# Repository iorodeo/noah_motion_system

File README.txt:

NOAH Motion System

Design files, software and firmware for the NOAH water tunnel motion control system.

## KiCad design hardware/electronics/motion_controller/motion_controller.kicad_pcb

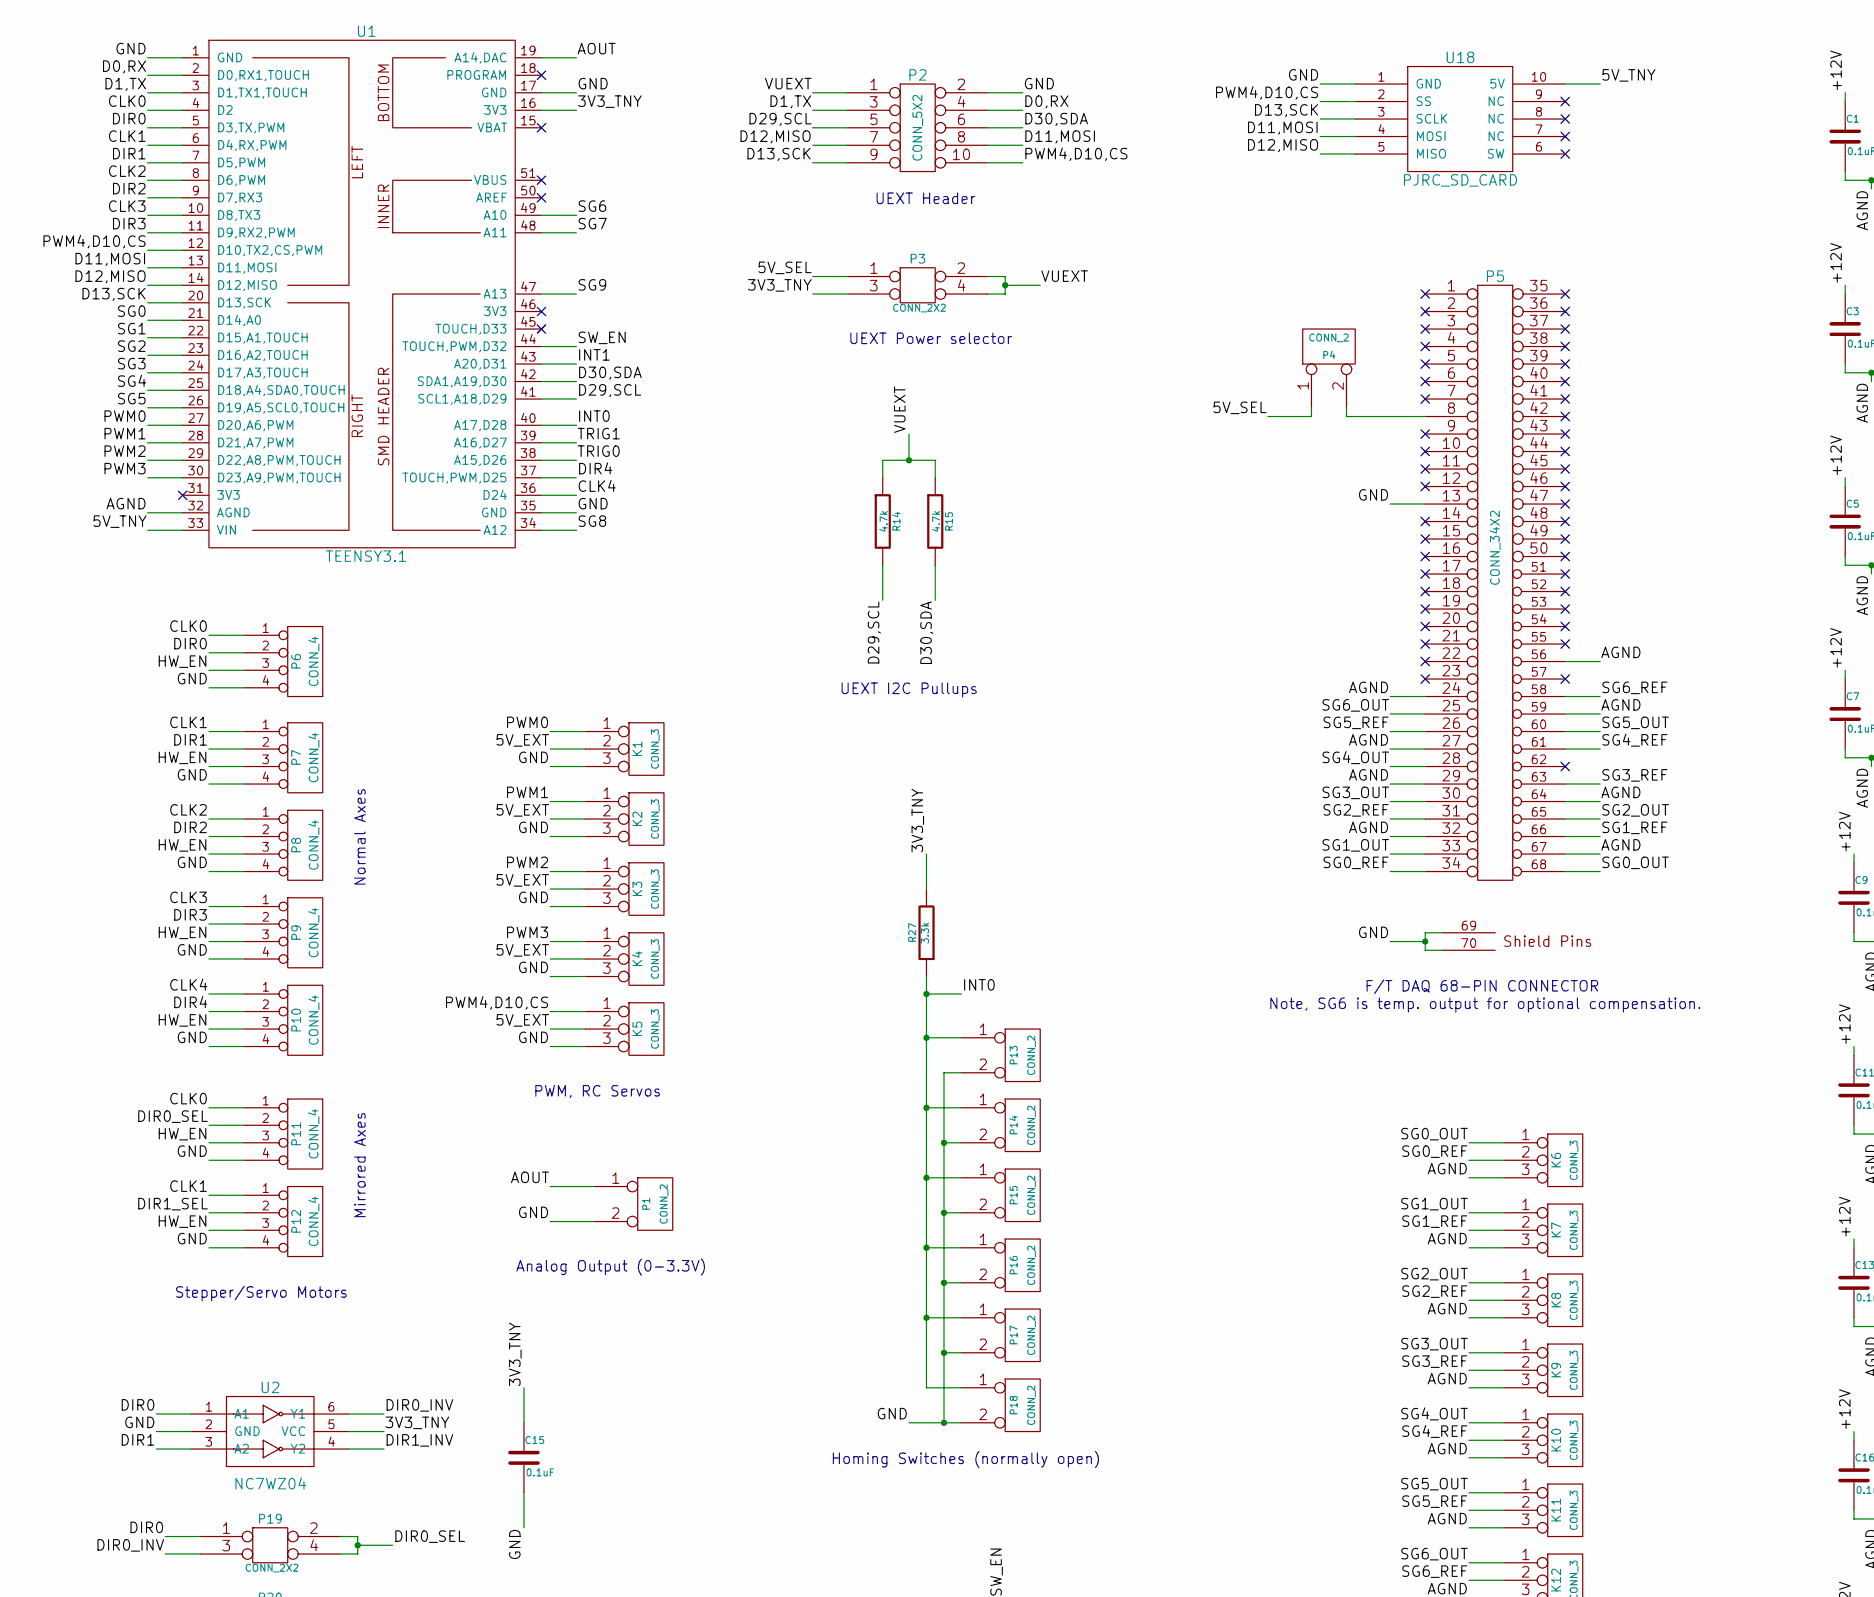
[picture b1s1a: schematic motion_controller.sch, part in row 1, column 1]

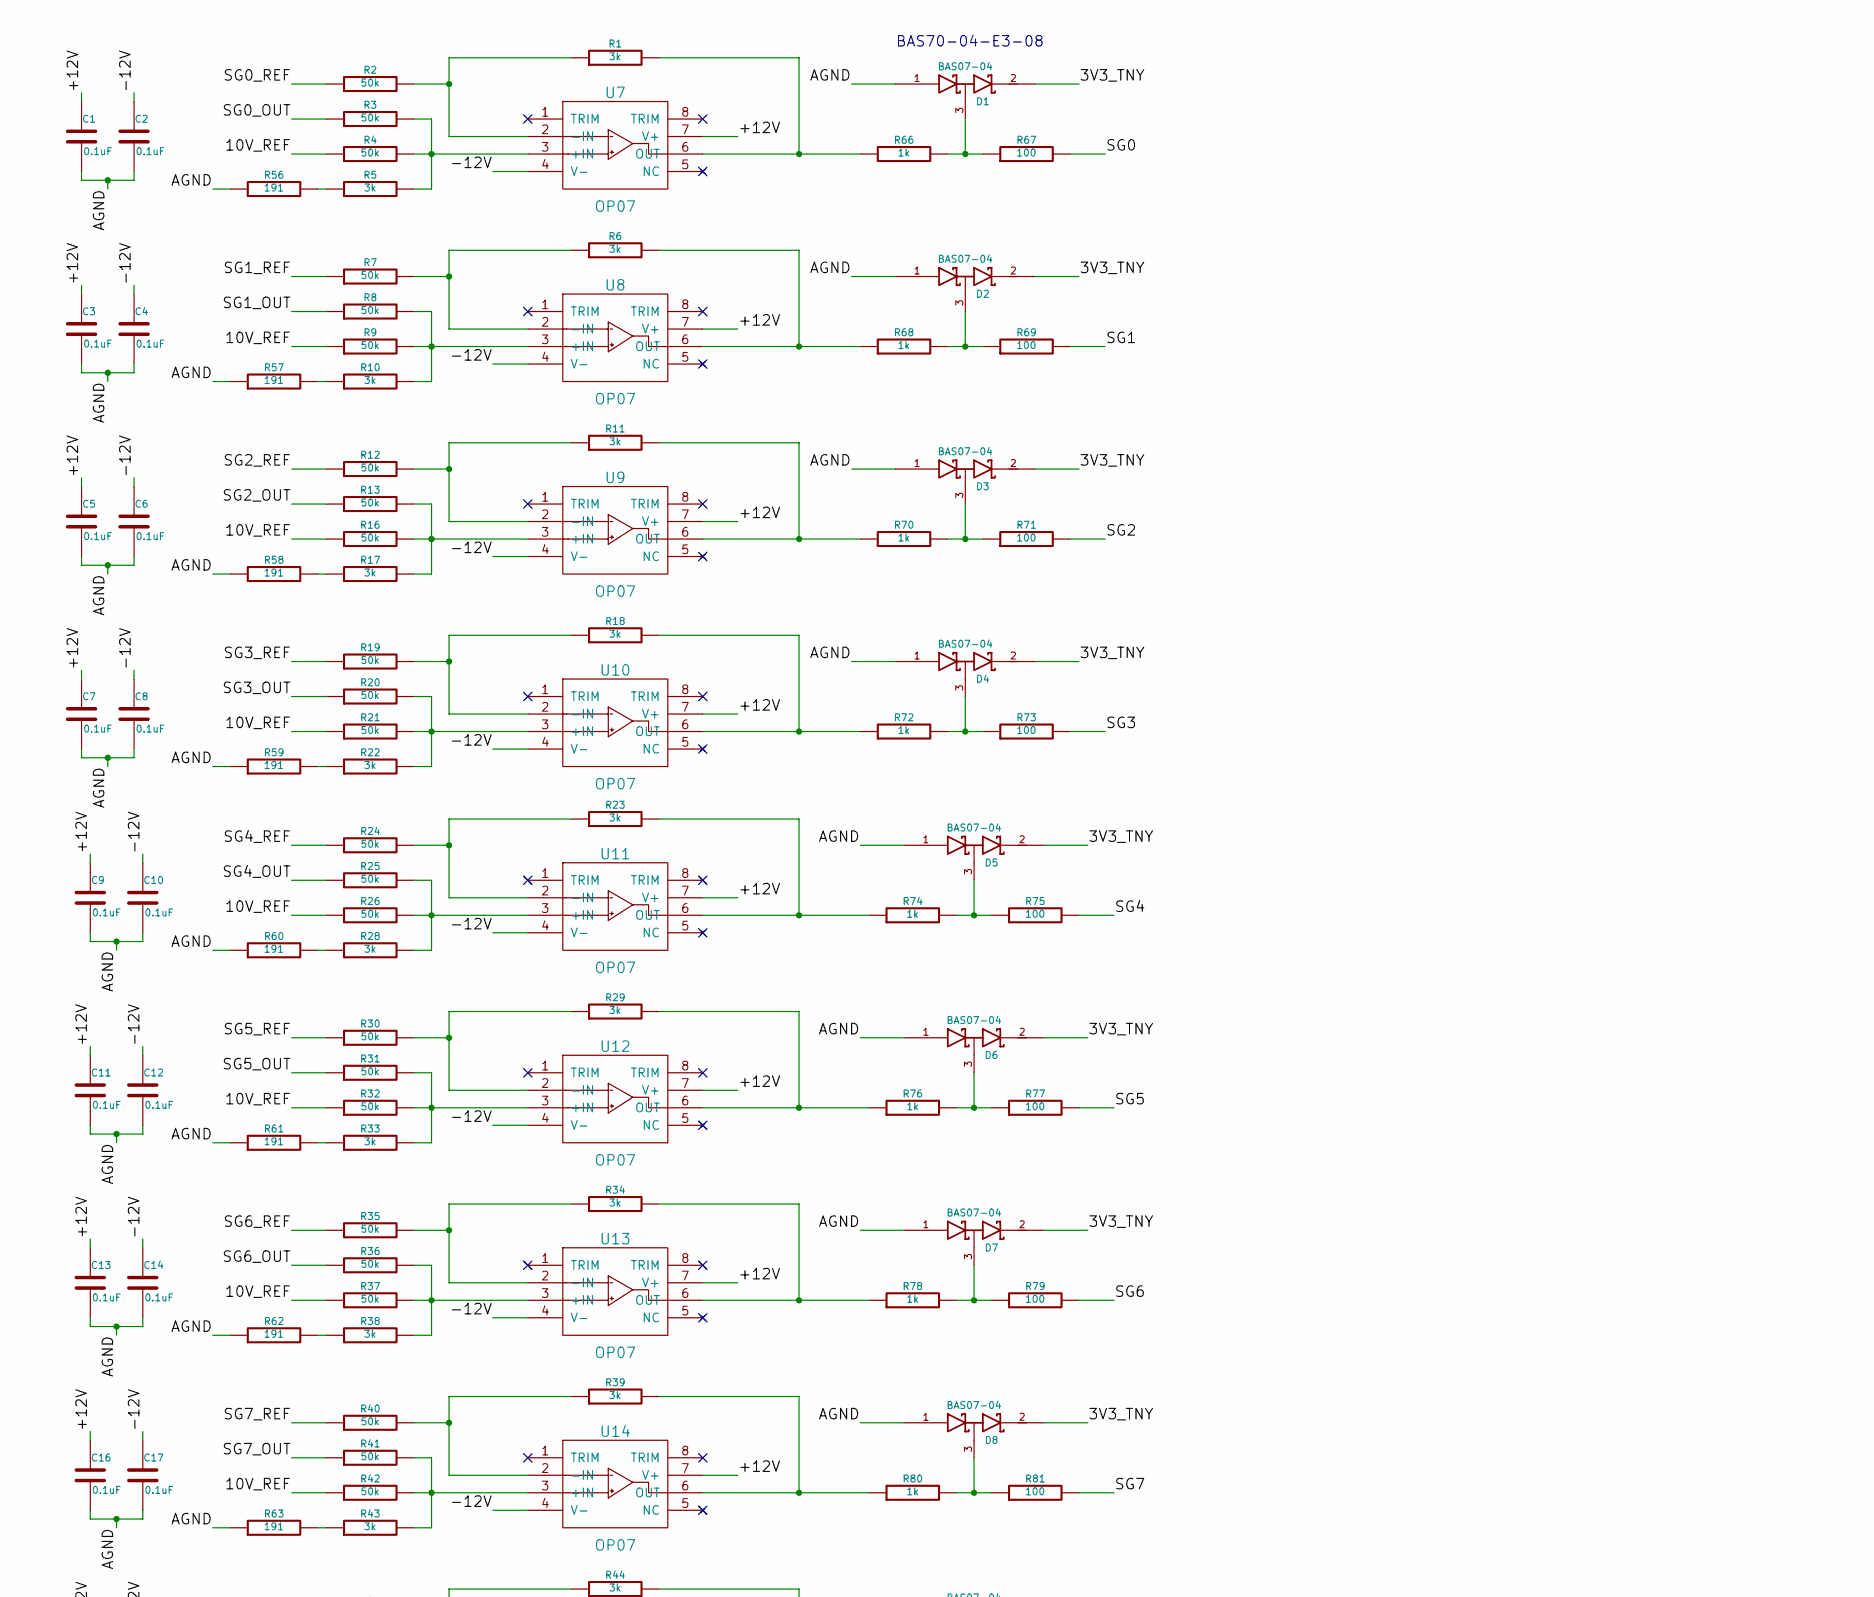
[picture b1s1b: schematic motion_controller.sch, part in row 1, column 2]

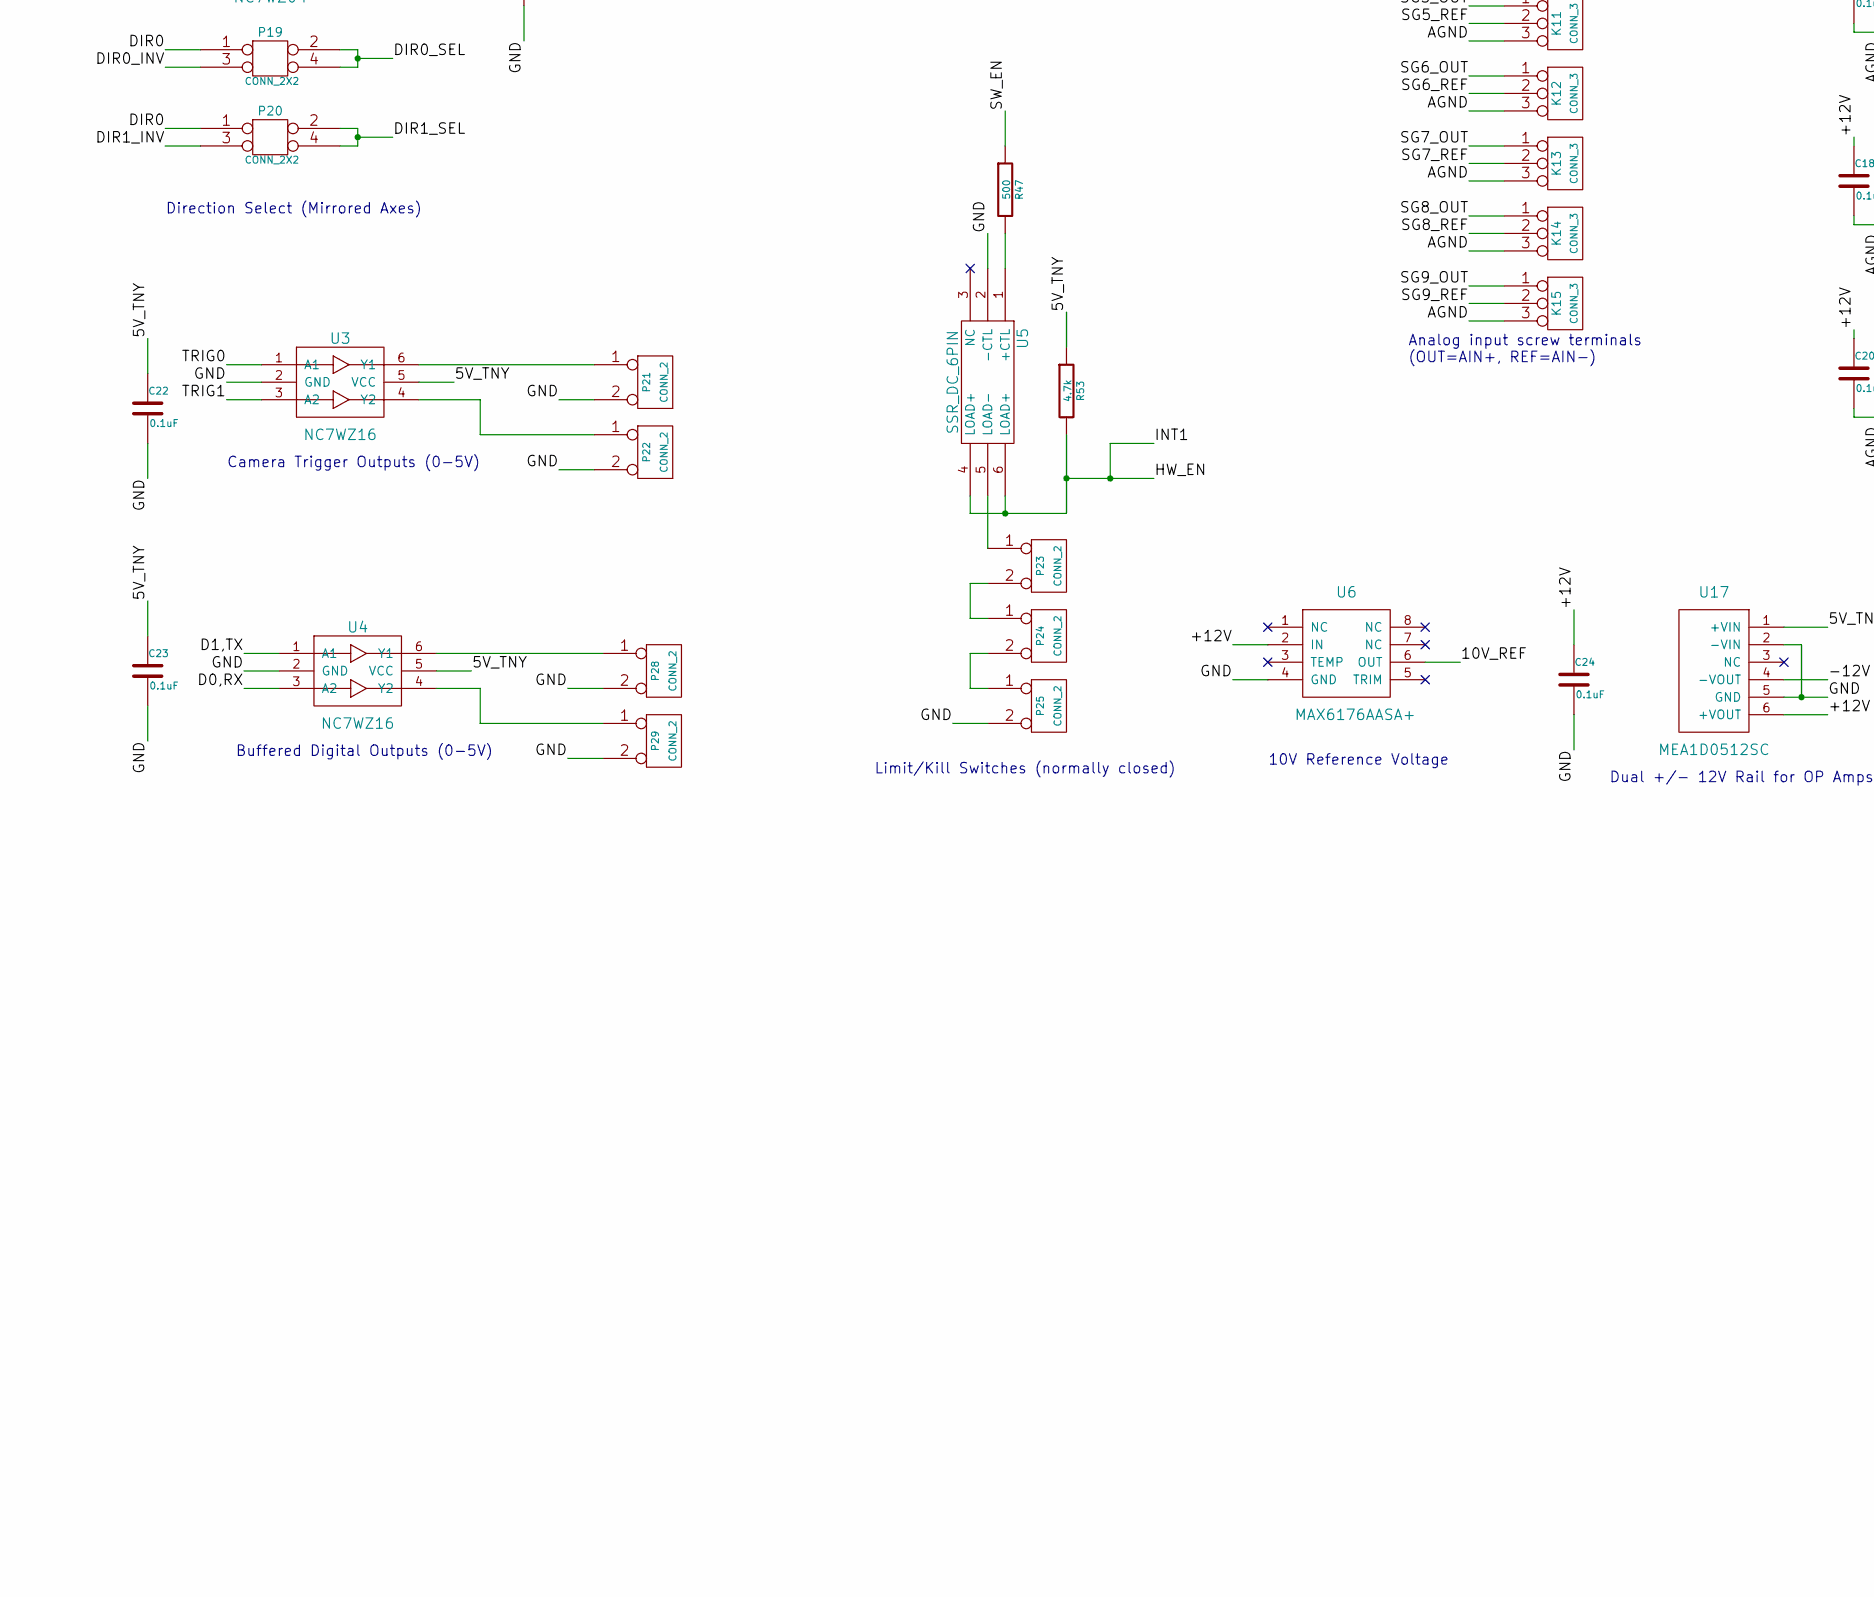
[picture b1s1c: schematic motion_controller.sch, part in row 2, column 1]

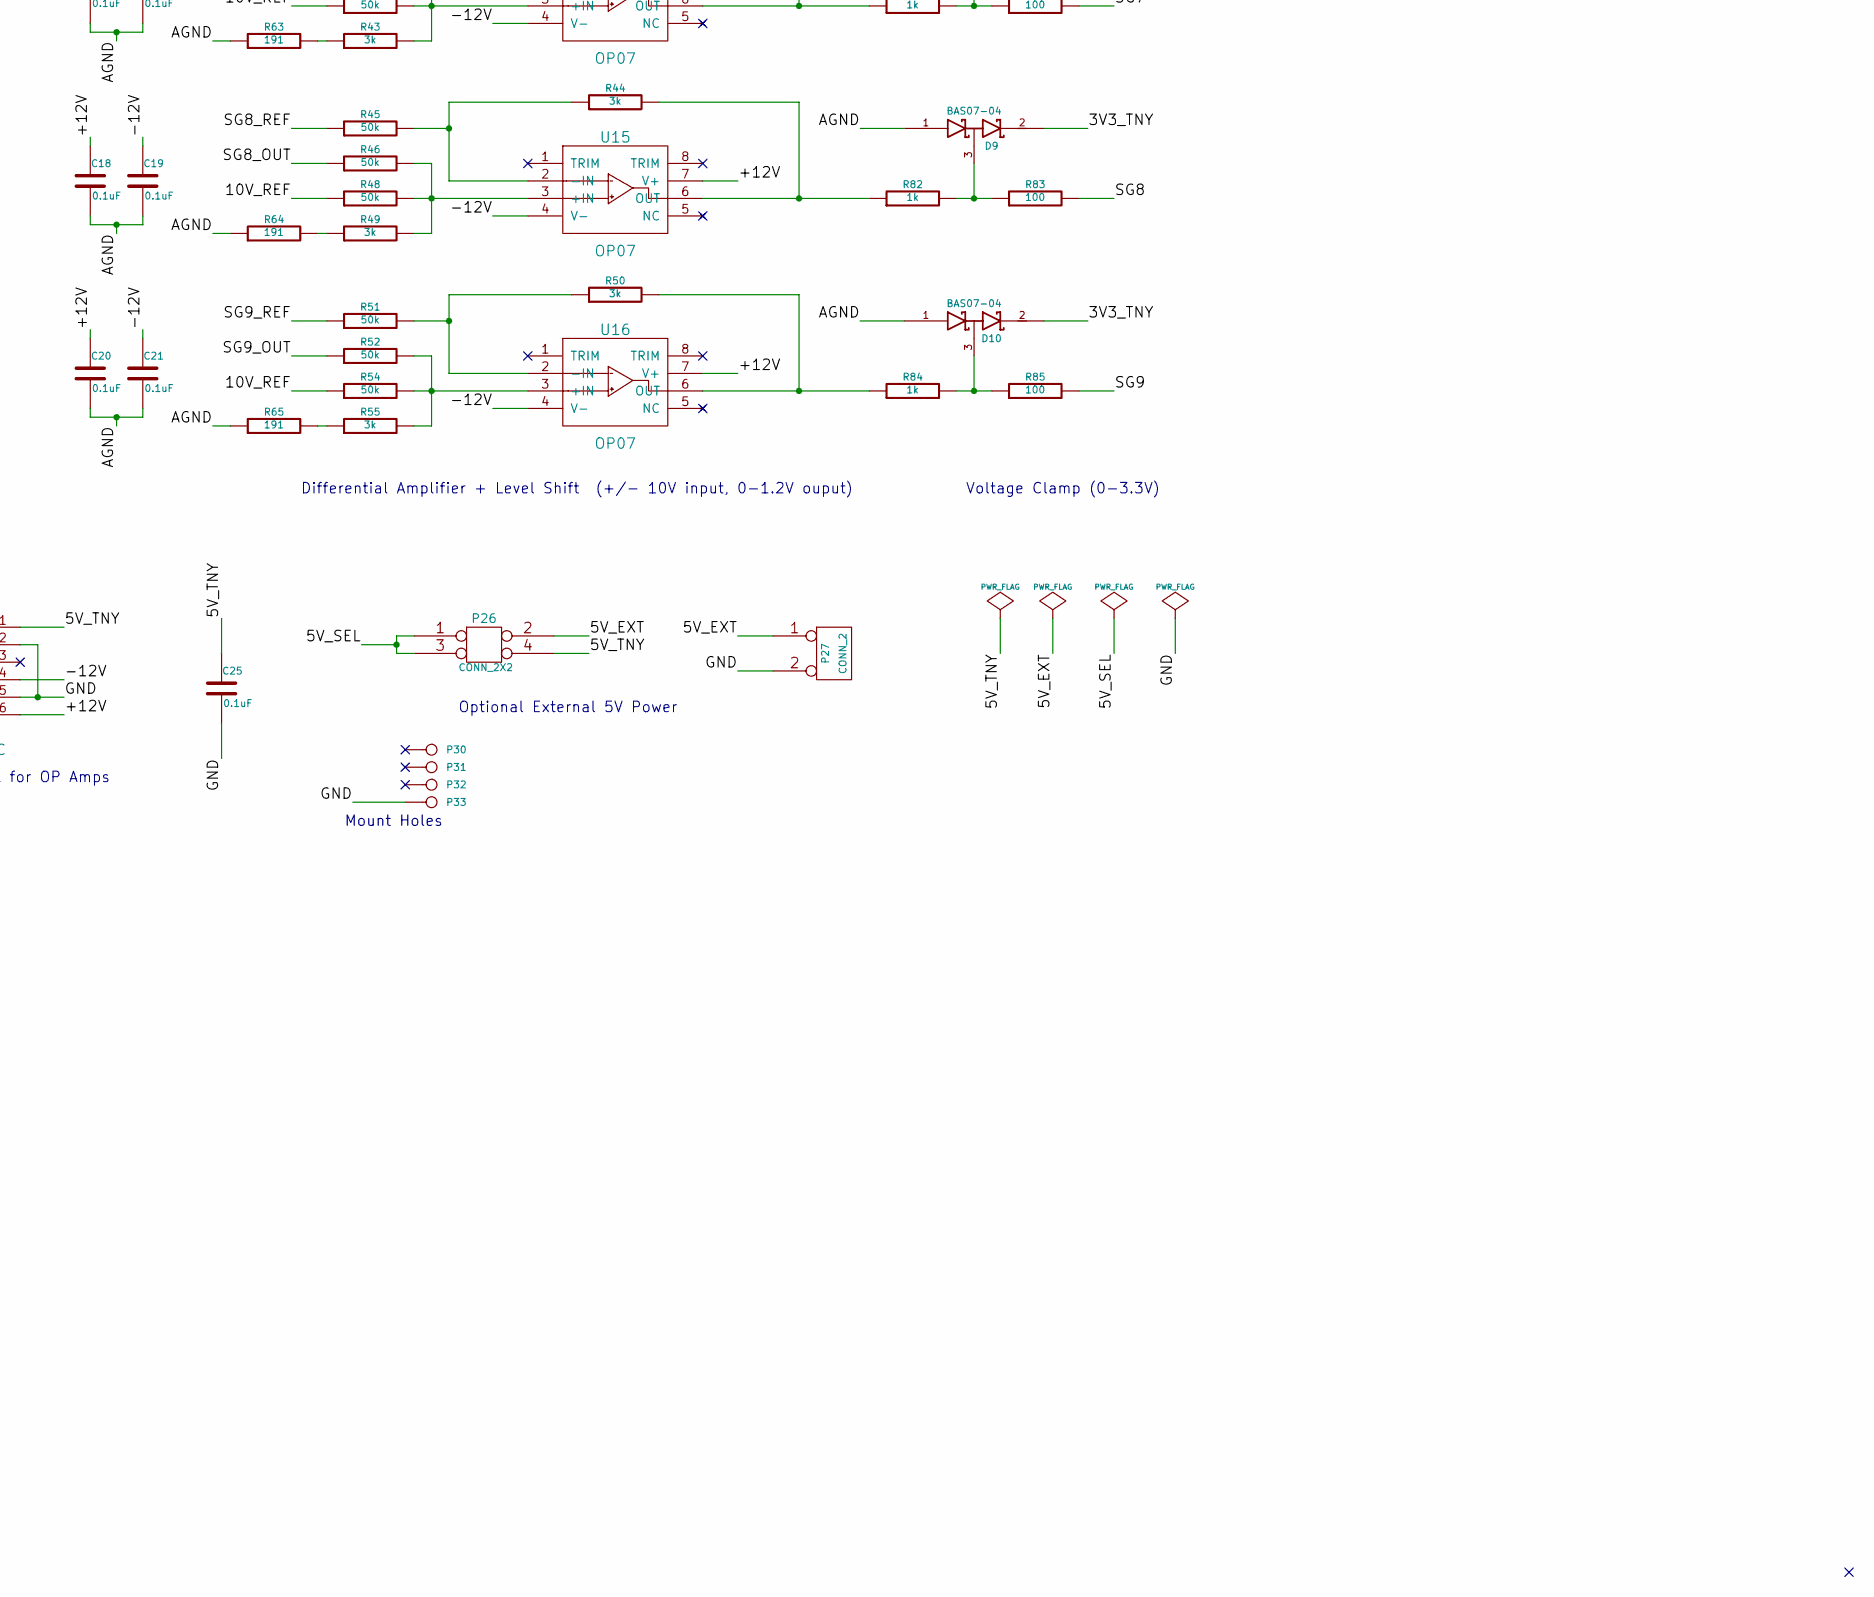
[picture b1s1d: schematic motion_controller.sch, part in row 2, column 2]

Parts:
C1, C2, C3, C4, C5, C6, C7, C8, C9, C10, C11, C12, C13, C14, C15, C16, C17, C18, C19, C20, C21, C22, C23, C24, C25: 0.1uF
D1, D2, D3, D4, D5, D6, D7, D8, D9, D10: BAS07-04
K1, K2, K3, K4, K5, K6, K7, K8, K9, K10, K11, K12, K13, K14, K15: CONN_3
P1, P4, P13, P14, P15, P16, P17, P18, P21, P22, P23, P24, P25, P27, P28, P29: CONN_2
P2: CONN_5X2
P3, P19, P20, P26: CONN_2X2
P5: CONN_34X2
P6, P7, P8, P9, P10, P11, P12: CONN_4
P30, P31, P32, P33: CONN_1
R1, R5, R6, R10, R11, R17, R18, R22, R23, R28, R29, R33, R34, R38, R39, R43, R44, R49, R50, R55: 3k
R2, R3, R4, R7, R8, R9, R12, R13, R16, R19, R20, R21, R24, R25, R26, R30, R31, R32, R35, R36, R37, R40, R41, R42, R45, R46, R48, R51, R52, R54: 50k
R14, R15, R53: 4.7k
R27: 3.3k
R47: 500
R56, R57, R58, R59, R60, R61, R62, R63, R64, R65: 191
R66, R68, R70, R72, R74, R76, R78, R80, R82, R84: 1k
R67, R69, R71, R73, R75, R77, R79, R81, R83, R85: 100
U1: TEENSY3.1
U2: NC7WZ04
U3, U4: NC7WZ16
U5: SSR_DC_6PIN
U6: MAX6176AASA+
U7, U8, U9, U10, U11, U12, U13, U14, U15, U16: OP07
U17: MEA1D0512SC
U18: PJRC_SD_CARD

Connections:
/3V3_TNY: C15.1, D1.2 (cathode), D2.2 (cathode), D3.2 (cathode), D4.2 (cathode), D5.2 (cathode), D6.2 (cathode), D7.2 (cathode), D8.2 (cathode), D9.2 (cathode), D10.2 (cathode), P3.3, R27.2, U1.16 (3V3), U2.5 (VCC)
/5V_EXT: K1.2 (PM), K2.2 (PM), K3.2 (PM), K4.2 (PM), K5.2 (PM), P26.2, P27.1
/5V_SEL: P3.1, P4.1, P26.1, P26.3
/5V_TNY: C22.1, C23.1, C25.1, P26.4, R53.1, U1.33 (VIN), U3.5 (VCC), U4.5 (VCC), U17.1 (+VIN), U18.10 (5V)
/10V_REF: R4.1, R9.1, R16.1, R21.1, R26.1, R32.1, R37.1, R42.1, R48.1, R54.1, U6.6 (OUT)
/+12V: C1.1, C3.1, C5.1, C7.1, C9.1, C11.1, C13.1, C16.1, C18.1, C20.1, C24.1, U6.2 (IN), U7.7 (V+), U8.7 (V+), U9.7 (V+), U10.7 (V+), U11.7 (V+), U12.7 (V+), U13.7 (V+), U14.7 (V+), U15.7 (V+), U16.7 (V+), U17.6 (+VOUT)
/-12V: C2.1, C4.1, C6.1, C8.1, C10.1, C12.1, C14.1, C17.1, C19.1, C21.1, U7.4 (V-), U8.4 (V-), U9.4 (V-), U10.4 (V-), U11.4 (V-), U12.4 (V-), U13.4 (V-), U14.4 (V-), U15.4 (V-), U16.4 (V-), U17.4 (-VOUT)
/AGND: C1.2, C2.2, C3.2, C4.2, C5.2, C6.2, C7.2, C8.2, C9.2, C10.2, C11.2, C12.2, C13.2, C14.2, C16.2, C17.2, C18.2, C19.2, C20.2, C21.2, D1.1 (Anode), D2.1 (Anode), D3.1 (Anode), D4.1 (Anode), D5.1 (Anode), D6.1 (Anode), D7.1 (Anode), D8.1 (Anode), D9.1 (Anode), D10.1 (Anode), K6.3, K7.3, K8.3, K9.3, K10.3, K11.3, K12.3, K13.3, K14.3, K15.3, P5.24, P5.27, P5.29, P5.32, P5.56, P5.59, P5.64, P5.67, R56.1, R57.1, R58.1, R59.1, R60.1, R61.1, R62.1, R63.1, R64.1, R65.1, U1.32 (AGND)
/AOUT: P1.1, U1.19 (A14,DAC)
/CLK0: P6.1, P11.1, U1.4 (D2)
/CLK1: P7.1, P12.1, U1.6 (D4,RX,PWM)
/CLK2: P8.1, U1.8 (D6,PWM)
/CLK3: P9.1, U1.10 (D8,TX3)
/CLK4: P10.1, U1.36 (D24)
/D0,RX: P2.4, U1.2 (D0,RX1,TOUCH), U4.3 (A2)
/D1,TX: P2.3, U1.3 (D1,TX1,TOUCH), U4.1 (A1)
/D11,MOSI: P2.8, U1.13 (D11,MOSI), U18.4 (MOSI)
/D12,MISO: P2.7, U1.14 (D12,MISO), U18.5 (MISO)
/D13,SCK: P2.9, U1.20 (D13,SCK), U18.3 (SCLK)
/D29,SCL: P2.5, R14.2, U1.41 (SCL1,A18,D29)
/D30,SDA: P2.6, R15.2, U1.42 (SDA1,A19,D30)
/DIR0: P6.2, P19.1, P20.1, U1.5 (D3,TX,PWM), U2.1 (A1)
/DIR0_INV: P19.3, U2.6 (Y1)
/DIR0_SEL: P11.2, P19.2, P19.4
/DIR1: P7.2, U1.7 (D5,PWM), U2.3 (A2)
/DIR1_INV: P20.3, U2.4 (Y2)
/DIR1_SEL: P12.2, P20.2, P20.4
/DIR2: P8.2, U1.9 (D7,RX3)
/DIR3: P9.2, U1.11 (D9,RX2,PWM)
/DIR4: P10.2, U1.37 (TOUCH,PWM,D25)
/GND: C15.2, C22.2, C23.2, C24.2, C25.2, K1.3, K2.3, K3.3, K4.3, K5.3, P1.2 (PM), P2.2, P5.13, P5.69, P5.70, P6.4, P7.4, P8.4, P9.4, P10.4, P11.4, P12.4, P13.2 (PM), P14.2 (PM), P15.2 (PM), P16.2 (PM), P17.2 (PM), P18.2 (PM), P21.2 (PM), P22.2 (PM), P25.2 (PM), P27.2 (PM), P28.2 (PM), P29.2 (PM), P33.1, U1.1 (GND), U1.17 (GND), U1.35 (GND), U2.2 (GND), U3.2 (GND), U4.2 (GND), U5.2 (-CTL), U6.4 (GND), U17.2 (-VIN), U17.5 (GND), U18.1 (GND)
/HW_EN: P6.3, P7.3, P8.3, P9.3, P10.3, P11.3, P12.3, R53.2, U1.43 (A20,D31), U5.4 (LOAD+), U5.6 (LOAD+)
/INT0: P13.1, P14.1, P15.1, P16.1, P17.1, P18.1, R27.1, U1.40 (A17,D28)
/PWM0: K1.1, U1.27 (D20,A6,PWM)
/PWM1: K2.1, U1.28 (D21,A7,PWM)
/PWM2: K3.1, U1.29 (D22,A8,PWM,TOUCH)
/PWM3: K4.1, U1.30 (D23,A9,PWM,TOUCH)
/PWM4,D10,CS: K5.1, P2.10, U1.12 (D10,TX2,CS,PWM), U18.2 (SS)
/SG0: R67.2, U1.21 (D14,A0)
/SG0_OUT: K6.1, P5.68, R3.1
/SG0_REF: K6.2 (PM), P5.34, R2.1
/SG1: R69.2, U1.22 (D15,A1,TOUCH)
/SG1_OUT: K7.1, P5.33, R8.1
/SG1_REF: K7.2 (PM), P5.66, R7.1
/SG2: R71.2, U1.23 (D16,A2,TOUCH)
/SG2_OUT: K8.1, P5.65, R13.1
/SG2_REF: K8.2 (PM), P5.31, R12.1
/SG3: R73.2, U1.24 (D17,A3,TOUCH)
/SG3_OUT: K9.1, P5.30, R20.1
/SG3_REF: K9.2 (PM), P5.63, R19.1
/SG4: R75.2, U1.25 (D18,A4,SDA0,TOUCH)
/SG4_OUT: K10.1, P5.28, R25.1
/SG4_REF: K10.2 (PM), P5.61, R24.1
/SG5: R77.2, U1.26 (D19,A5,SCL0,TOUCH)
/SG5_OUT: K11.1, P5.60, R31.1
/SG5_REF: K11.2 (PM), P5.26, R30.1
/SG6: R79.2, U1.49 (A10)
/SG6_OUT: K12.1, P5.25, R36.1
/SG6_REF: K12.2 (PM), P5.58, R35.1
/SG7: R81.2, U1.48 (A11)
/SG7_OUT: K13.1, R41.1
/SG7_REF: K13.2 (PM), R40.1
/SG8: R83.2, U1.34 (A12)
/SG8_OUT: K14.1, R46.1
/SG8_REF: K14.2 (PM), R45.1
/SG9: R85.2, U1.47 (A13)
/SG9_OUT: K15.1, R52.1
/SG9_REF: K15.2 (PM), R51.1
/SW_EN: R47.1, U1.44 (TOUCH,PWM,D32)
/TRIG0: U1.38 (A15,D26), U3.1 (A1)
/TRIG1: U1.39 (A16,D27), U3.3 (A2)
/VUEXT: P2.1, P3.2, P3.4, R14.1, R15.1
unnamed: P21.1, U3.6 (Y1)
unnamed: R47.2, U5.1 (+CTL)
unnamed: P23.1, U5.5 (LOAD-)
unnamed: P29.1, U4.4 (Y2)
unnamed: P28.1, U4.6 (Y1)
unnamed: P22.1, U3.4 (Y2)
unnamed: P23.2 (PM), P24.1
unnamed: P24.2 (PM), P25.1
unnamed: R20.2, R21.2, R22.2, U10.3 (+IN)
unnamed: R18.2, R72.1, U10.6 (OUT)
unnamed: R18.1, R19.2, U10.2 (-IN)
unnamed: R13.2, R16.2, R17.2, U9.3 (+IN)
unnamed: R11.2, R70.1, U9.6 (OUT)
unnamed: R29.2, R76.1, U12.6 (OUT)
unnamed: R25.2, R26.2, R28.2, U11.3 (+IN)
unnamed: R23.2, R74.1, U11.6 (OUT)
unnamed: R23.1, R24.2, U11.2 (-IN)
unnamed: R1.2, R66.1, U7.6 (OUT)
unnamed: R1.1, R2.2, U7.2 (-IN)
unnamed: R11.1, R12.2, U9.2 (-IN)
unnamed: R8.2, R9.2, R10.2, U8.3 (+IN)
unnamed: R6.2, R68.1, U8.6 (OUT)
unnamed: R6.1, R7.2, U8.2 (-IN)
unnamed: R3.2, R4.2, R5.2, U7.3 (+IN)
unnamed: R33.1, R61.2
unnamed: R49.1, R64.2
unnamed: R43.1, R63.2
unnamed: R38.1, R62.2
unnamed: R28.1, R60.2
unnamed: R22.1, R59.2
unnamed: R17.1, R58.2
unnamed: R10.1, R57.2
unnamed: P4.2 (PM), P5.8
unnamed: D1.3 (AK), R66.2, R67.1
unnamed: R55.1, R65.2
unnamed: R50.1, R51.2, U16.2 (-IN)
unnamed: R5.1, R56.2
unnamed: D4.3 (AK), R72.2, R73.1
unnamed: D3.3 (AK), R70.2, R71.1
unnamed: D6.3 (AK), R76.2, R77.1
unnamed: D5.3 (AK), R74.2, R75.1
unnamed: D2.3 (AK), R68.2, R69.1
unnamed: R34.2, R78.1, U13.6 (OUT)
unnamed: D10.3 (AK), R84.2, R85.1
unnamed: D8.3 (AK), R80.2, R81.1
unnamed: R39.2, R80.1, U14.6 (OUT)
unnamed: D7.3 (AK), R78.2, R79.1
unnamed: D9.3 (AK), R82.2, R83.1
unnamed: R50.2, R84.1, U16.6 (OUT)
unnamed: R44.2, R82.1, U15.6 (OUT)
unnamed: R46.2, R48.2, R49.2, U15.3 (+IN)
unnamed: R36.2, R37.2, R38.2, U13.3 (+IN)
unnamed: R34.1, R35.2, U13.2 (-IN)
unnamed: R31.2, R32.2, R33.2, U12.3 (+IN)
unnamed: R29.1, R30.2, U12.2 (-IN)
unnamed: R41.2, R42.2, R43.2, U14.3 (+IN)
unnamed: R44.1, R45.2, U15.2 (-IN)
unnamed: R39.1, R40.2, U14.2 (-IN)
unnamed: R52.2, R54.2, R55.2, U16.3 (+IN)

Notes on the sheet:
F/T DAQ 68-PIN CONNECTOR
Note, SG6 is temp. output for optional compensation.
Analog input screw terminals (OUT=AIN+, REF=AIN-)
UEXT Header
UEXT Power selector
Homing Switches (normally open)
Limit/Kill Switches (normally closed)
Optional External 5V Power
PWM, RC Servos
Camera Trigger Outputs (0-5V)
UEXT I2C Pullups
Buffered Digital Outputs (0-5V)
Stepper/Servo Motors
Differential Amplifier + Level Shift (+/- 10V input, 0-1.2V ouput)
Normal Axes
Mirrored Axes
Dual +/- 12V Rail for OP Amps
10V Reference Voltage
Voltage Clamp (0-3.3V)
Analog Output (0-3.3V)
Direction Select (Mirrored Axes)
BAS70-04-E3-08
Mount Holes

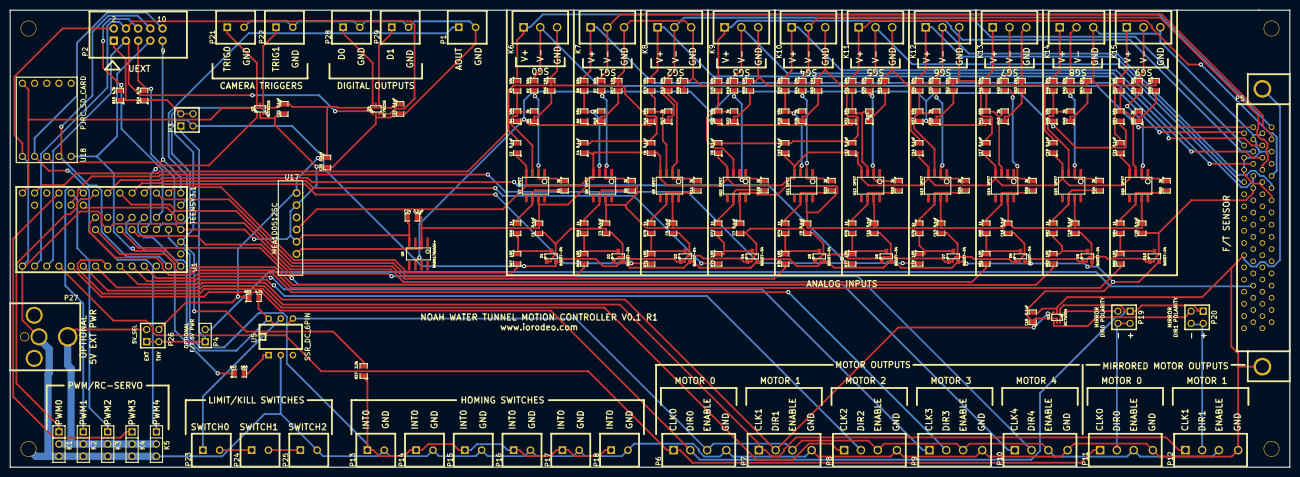
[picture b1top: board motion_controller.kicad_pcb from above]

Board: 2 copper layers, 266.7 x 95.3 mm, 186 parts (0 on the bottom side), 131 nets.

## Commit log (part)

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2015-11-16 Project creation.
2015-11-16 Added readme.
2015-11-16 Fixed capitalization in readme.
2015-11-17 Added further output to usb_timer_test.py
2015-11-30 Added design for gantry carriage plate.
2015-12-01 Added separate drawings of carriage and gantry plates.
2015-12-01 Changed directory name.
2016-02-16 Added rawhid tests.
2016-02-16 Added license information.
2016-03-01 Worked on motor controller demo.
2016-03-01 Added motion controller class to host example.
2016-03-02 Added captive trajectory capability via command line args to demo.
2016-03-02 Added joystick number hack.
2016-03-02 Added display to teensy code.
2016-03-02 Minor changes.
2016-03-02 Cleanup up a bit. Slowed down clk/dir loop.
2016-03-02 Fixed bug in Stepper class step update.
2016-03-02 Tweaked trajectory for demo.
2016-04-02 Fixed motion controller schem. so that design rules check is satisfied. Addd 2nd resistor to differential amplifier - to make it easy to find components with correct values.
2016-04-05 Changed clamping circuit. Worked on footprint assignment.
2016-04-05 Finished footprint association.
2016-04-07 Worked on motion controller PCB layout.
2016-04-08 Worked on layout of analog input subsystem.
2016-04-08 Added PJRC SD card. Changed so that double schottky diodes in a analog clamp use AGND instead of GND. Worked on layout.
2016-04-09 Finished preliminary routing of motion controller PCB.
2016-04-10 Worked on motion controller PCB annotation, routing and layout.
2016-04-11 Finished motion controller pcb annotation and re-routed board.
2016-04-11 Modified motion controller pcb slightly - made so that only one mounting hole is grounded.
2016-04-11 Added .zip archive for motion_controller pcb V0.1 R1 gerber files.
2016-04-14 Worked on BOM for motion controller PCB.
2016-04-15 Re-worked differential amplifier op amp bias network symbolic algebra calculation to use solveset instead of solve.
2016-04-15 Worked on BOM.
2016-04-16 Finished motion controller PCB BOM.
2016-05-05 Fixed part issue in BOM - specified 8-SO rather than 8-SOIC.
2016-05-31 Added some simple firmware tests for new motion controller pcb.
2016-06-23 Modified gantry mount plate design.
2016-07-02 Renamed directory.
2016-07-02 Added design for limit switch mount plates.
2016-07-02 Added lasercutting layout for limit switch mounts.
2016-07-03 Added second limit switch mount design + laser cutting layout.
2016-07-03 Renamed limit switch gcode file.
2016-07-03 Fixed issue with limit switch mount type2 design. Added gcode for laser cutting..
2016-07-18 Fixed issue with rotary axis mount plate. Worked on force sensor mount.
2016-07-18 Fixed rotary axis mount in waterjet layout.
2016-07-18 Finished initial design of force sensor to model adapter plates.
2016-07-22 Rearranged mechanics directories.
2016-07-22 Added design and gcode generation for power switch plate.
2016-07-22 Made minor modifications for power_switch_plate gcode gen. Made gcode for cutting.
2016-07-23 Worked on power supply mount plate.
2016-07-25 Worked on electronic mounting plates.
2016-07-27 Finished design of main electronics mount plate.
2016-07-28 Removed pocket_drill anded proper peck drills for cuttinb bulkhead connector mount plates.
2016-07-30 Added designs for mdf backing plates and clear acrylic cover plates.
2016-07-30 Added gcode generation for power supply mount plate.
2016-07-31 Added gcode generation for electronics mount main plate.
2016-07-31 Added dimensions to eleectronics mount main plate cnc layout file.
2016-07-31 Added gcode for cutting main electronics mount plate.
2016-08-03 Added design for upper and lower gantry foot plates.
2016-08-03 Added cnc layout for gantry mdf riser blocks.
2016-08-04 Added cnc for cutting 0.25in mdf riser blocks.
2016-08-14 Worked on firmware and software.
2016-08-14 Modified rawhid message types.
2016-08-15 Worked on firmware. Added stepper class and continued to flush out constants for triggering, steppers, pwm, etc. Worked on SystemState class and timer updates.
2016-08-16 Worked on motion controller.
2016-08-16 Worked on controller firmware - added Trigger class for handling camera triggers.
2016-08-16 Worked on firmware. Added velocity controller. Added bounds checking to steppers - last resort hard stop.
2016-08-17 Worked on firmware. Flushed out velocity controller.
2016-08-17 Added notes to velocity controller's update function.
2016-08-19 Fixed issues with HomingController. Added EStopMonitor.
2016-08-19 Worked on firmware. Modified update functions for motion mode controllers so that is returns new velocity as this makes things a little cleaner. Work on modes and communications.
2016-08-20 Flushed out rawhid comms for homing and positioning modes. Fixed issue with EStopMonitor - need delay after turn on and signal change isnt' super quick.
2016-08-23 Worked on firmare and host software. Flushed on host side homing and positioning commands.
2016-08-23 Change some of the range loops so that they use auto.
2016-08-23 Caught missing range loop no using auto.
2016-08-23 Worked on motion::Controller and motion::MotionConfig.
2016-08-24 Worked motion::Controller and configuration.
2016-08-24 Added depenency on Armadillo library - used for outscan and outscan data. Work on outscan methods.
2016-08-24 Worked on adding ability to use Armadillo matrices in motion::Controller.
2016-08-24 More work on jogging and positioning moves. Added position display.
2016-08-25 Worked motion controller trajectory outscaning.
2016-08-25 Cleaned up motion controller outscan method.
2016-08-25 Fixed bug in outscan method when checking the set velocity control mode has been received..
2016-08-28 Worked on outscan methonds.
2016-08-29 Work on motion controller outscan from file.
2016-08-29 Worked on command line app.
2016-08-29 Worked on command line interface.
2016-09-04 Modified x axis homing direction. Modified test trajectory.
2016-09-04 Added additional comments to cmd_line_app.
2016-09-04 Added help command to command line app.
2016-09-06 Worked on OutscanData class.
2016-09-07 Worked on data logging.
2016-09-07 Worked on logging.
2016-09-07 Worked on OutscanData logging methods.
2016-09-08 Worked on OutscanData class logging.
2016-09-08 Worked on hdf5 file creation for OutscanData.
2016-09-08 Workd on OutscanData save to hdf5.
2016-09-09 More work on OutscanData. Add datetime attribute to root level group.
2016-09-10 Added exception handling for HDF5 file access in OutscanData.
2016-09-10 Cleaned up motion_controller a bit.
2016-09-11 Modified for building on rpi. Working through some issues with rawhid on the rpi.
2016-09-11 Added temporary check on raw hid device nums.
2016-09-11 Minor tweak to clearRecvBuffer.
2016-09-11 Removed test from firmware.
2016-09-13 Worked on command line app. Cleaned up - removed some redundancy. Worked move-to-ind command.
2016-09-13 Renamed test example.
2016-09-15 Cleaned up CMakeLists a bit.
2016-09-15 Re-naming and re-organizing software and firmware files.
2016-09-16 More work on project structure.
2016-09-16 Added LICENSE file.
2016-09-16 Additional work on project structure. Added -o option to command line app.
2016-09-16 Added atidaq library.
2016-09-20 Work on six axis force torque convertion.
2016-09-21 Add FT_ToolTransform for FT_SensorCal.
2016-09-21 Worked on six axis sensor force torque conversions.
2016-09-21 Further work on FT_SensorCal and FT_ToolTransform. Added getters for units. Add ability to set bias vector.
2016-09-21 Finished preliminary version of FT_SensorCal.
2016-09-22 Finished get_info_string method for FT_SensorCal.
2016-09-22 Added print_info method to FT_SensorCal class.
2016-09-22 Worked on configuration loader.
2016-09-23 Worked on methods for loading configuration from json file. Added example config.json and force/torque sensor calibration.
2016-09-23 Worked on methods for loading configuration from json file.
2016-09-23 Added command to display force torque sensor information.
2016-09-24 Worked on analog_input to force/torque conversion in outscan data. Added automatic setting of temperature compensation if available. Fixed bug in FT_SensorCal which made is_initialized always return 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
2016-09-28 Added basic structure for command line help system.
2016-09-28 Modified OutscanData so that force and torque units are added as an attribute to the force_and_torque data set in the hdf5 output file.
2016-09-29 Fixed CMakeLists for mcontrol and devel apps so that the build works on the rpi.
2016-09-29 Added stubs for additional mcontrol commands.
2016-10-01 Added joystick information to json configuration file.
2016-10-01 Updated json configuration file example.
2016-10-02 Added addition items to configuration file. Such as outscan start delay, outscan number of bias samples, the joystick device, the joystick axis mapping, the joystick invert table. Add addition comman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
2016-10-02 Modified mcontrol command app so that exit codes are set correctly.
2016-10-02 Worked on additonal commands for mcontrol eg. get-ai-samples, ..., set-trigger-freq, etc.
2016-10-02 Finished command to enable/disable hardware trigger and check hardware trigger state. Added license files.
2016-10-03 Added additional commands to set boundaries, speeds, etc.
2016-10-03 Update example configuration file.
2016-10-03 Added commands for setting device configuration - min_position, max_postion, max_speed, max_accel, homing_direction.
2016-10-03 Added license for included joystick class.
2016-10-03 Added joystick_pendant method to Controller and mcontrol 'joystick' command. Added joystick velocity settings to json configuration.
2016-10-03 Modified so that correct return code is set when quiting via Ctrl-C. This way scrips terminate properly.
2016-10-04 Modified json configuration. Add force torque sensor calibration from NOAH sensor.
2016-10-04 Added test for isInitialState when reading events from joystick in joystick_pendant method. This seems to prevent the issue of reading garbage when the joystick is first connected.
2016-10-04 Added methods and mcontrol commands for getting/displaying forces and torques.
2016-10-04 Added example scripts.
2016-10-04 Added c++ api example.
2016-10-04 Fixed issue with get_ai/get_ft ai_display/ft_display methods - added missing calls to clearReceiveBuffer.
2016-10-04 Modifications for controller.cpp - debugging homing issue.
2016-10-05 Fixed firmware bug which caused homing failure when all axes where not already homed.
2016-10-05 Worked on home issue - fixed a few more issues.
2016-10-05 Add additional test to basic moves. Added new test trajectory.
2016-10-20 Modified homing so that axes are backed off of the homing switches before and after homing.
2016-10-20 Modified firmware and software so that device configuration can be stored in eeprom.
2016-10-20 Added checks on size ind_speed and ind_accel prior to conversion to uint16_t. Note, may want to modify this as it is limiting our accelerations.
2016-10-25 Updated software and firmware so that digital outputs can be included in the outscan trajectory.
2016-10-27 Added usb command for checking homing pin state. Added controller method and program command for checking homing pin state. Modified software so that after the pre-homing backoff the home pin state i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
2016-11-10 Fixed bug in string stream output.
2016-11-10 Fixed compilation issue - finding hdf5
2016-11-10 Add udev rules for teensy.
2016-12-08 Added layout for cutting type3 and type4 limit switch mounting brackets.
2016-12-08 Added gcode for cutting type 3 and 4 limit switch mounting brackets.
2017-02-24 Added design for new limit switch mount.
2017-04-04 Added some captive trajectory examples.
2017-04-04 Worked on captive trajectory examples.
2017-04-11 Worked on captive trajectory api - simplified so that users don't have to do as much extraction.
2017-04-12 Cleaned up comments a bit more.
2017-06-29 Added notes for building and installing software.
2017-06-29 Moved noah_build_notes.txt to install.txt.
2017-08-15 Increase size of object sent by socket.io test clent to 50 items as test.
2017-10-02 Added gain to json configuration.
2017-10-02 Added "gain" to example config.json.
